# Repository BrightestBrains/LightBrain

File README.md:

# LightBrain

## Overview

The initial motivation was to develop a compact and relatively versatile light control device. Communicating with colleagues interested in electronics, I made a few design decisions so that the functionality would meet a number of requests: wide power supply voltages, protection, buttons, DMX support, shifted ouputs.

* ESP32-WROOM module
* four level shifted outputs
* 6-30V protected power input
* RS485 chip (DMX Support)
* Convinent buttons and user LED
* Very handy WAGO spring terminals

## Usage

Designed mostly for the usage with [WLED firmware](https://github.com/Aircoookie/WLED) by [Aircookie](https://github.com/Aircoookie)

There is no USB=>UART bridge in design. This was done to make the design smaller and cheaper. In the future, a firmware device with pogopin will be made, but most likely there will be a revision of the entire design. WLED has OTA functionality which can be used in case of update the firmware.

The board comes with a few examples that I wrote to test the functionality of the board. I really like [micropython](https://micropython.org/), which works fine on these boards. Very handy for prototyping, the buttons and custom LED makes it interactive. Unfortunately, I never got around to running DMX with python. Then I wrote an example using the SparkFunDMX library, which works like a charm.

## Appearance and Examples

Illustration of working WLED:

https://user-images.githubusercontent.com/8849896/159166993-72adfaef-fdb5-461d-86bc-35848b8165a1.mp4

https://user-images.githubusercontent.com/8849896/159166995-e5065d50-ee23-4bfb-9fdf-d8251501cd79.mp4

https://user-images.githubusercontent.com/8849896/159166997-b3421e14-9344-47e1-aa16-2b2efedc7f29.mp4

Illustration of working DMX:

https://user-images.githubusercontent.com/8849896/159167005-f4b18b29-a19e-47f2-82c6-617aa11a5b83.mp4

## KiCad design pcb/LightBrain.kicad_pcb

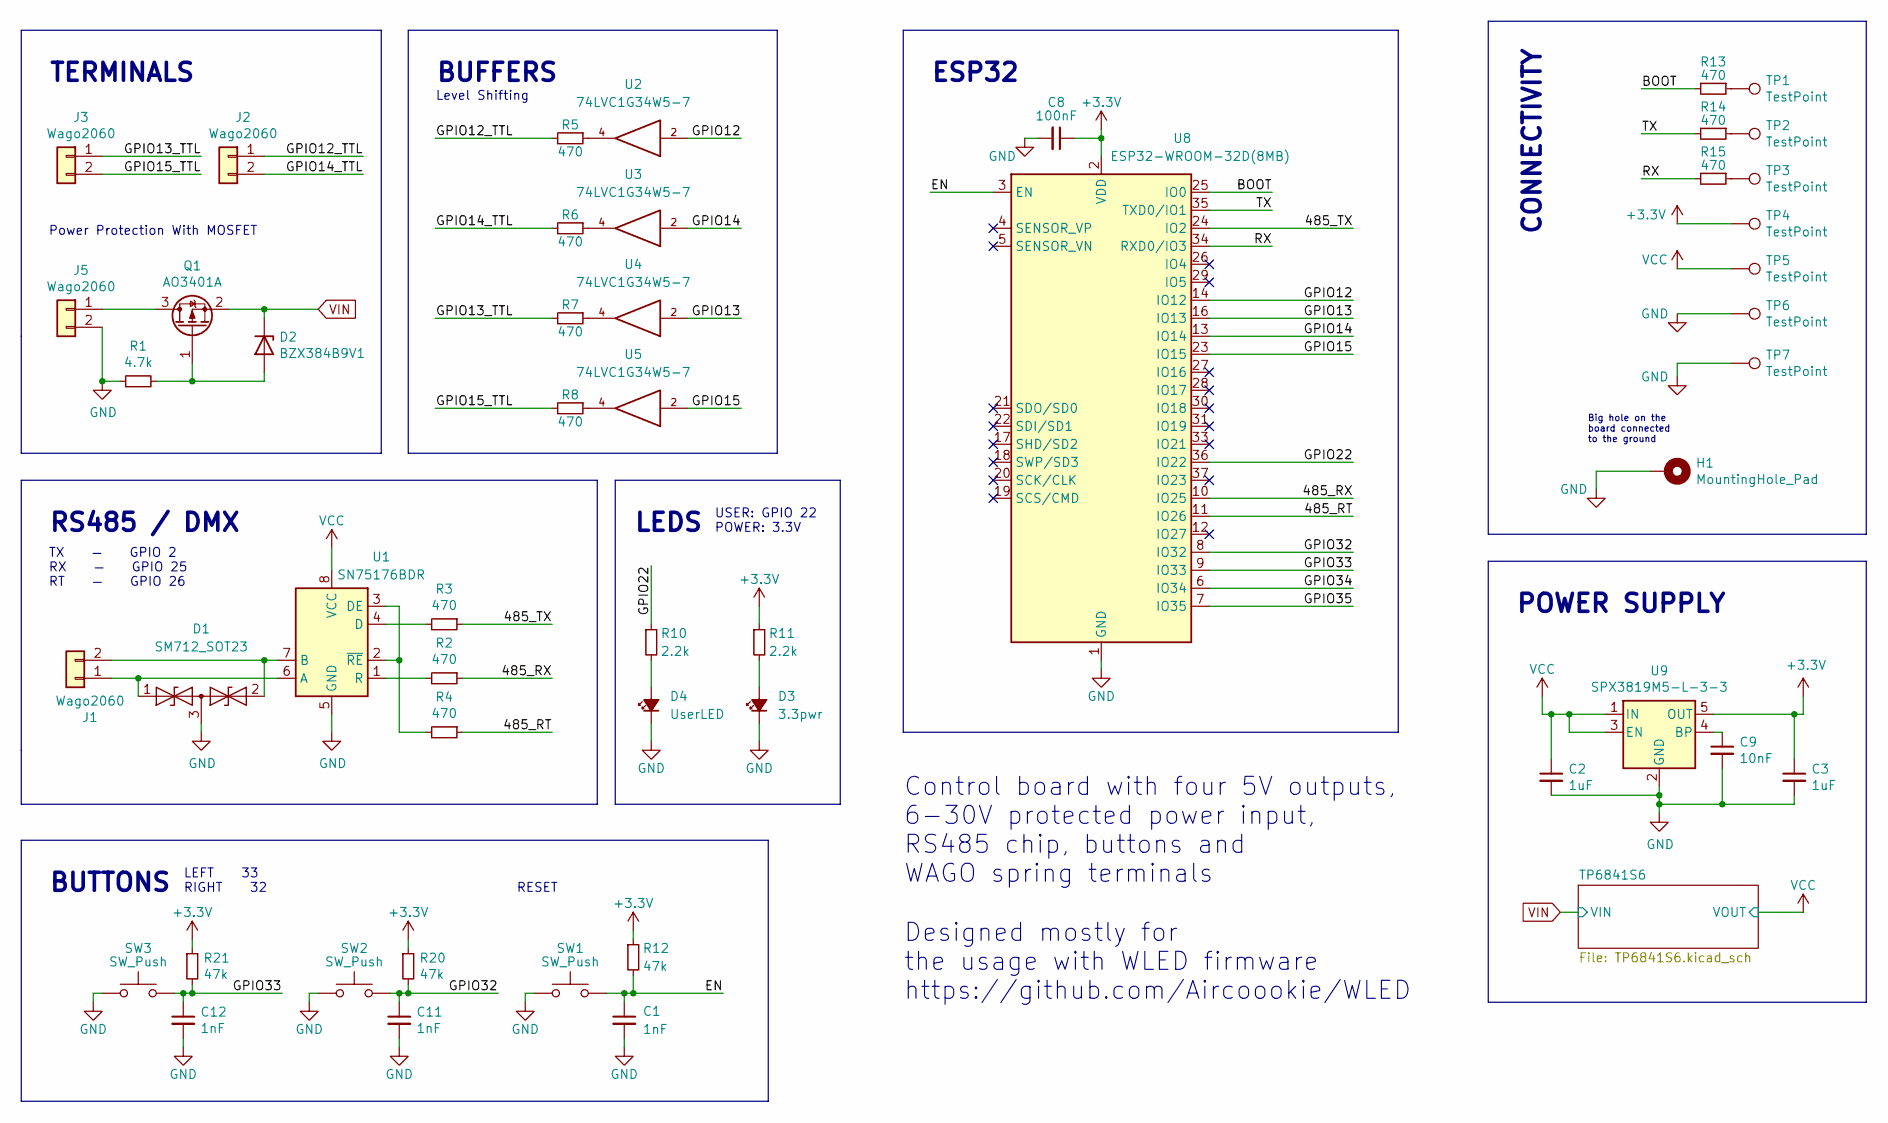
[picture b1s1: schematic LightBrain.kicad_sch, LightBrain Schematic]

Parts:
C1, C11, C12: 1nF; C_0402_1005Metric; JLCPCB Part # C1523
C2, C3: 1uF; C_0402_1005Metric; JLCPCB Part # C52923
C8: 100nF; C_0402_1005Metric; JLCPCB Part # C307331
C9: 10nF; C_0402_1005Metric; JLCPCB Part # C15195
D1: SM712_SOT23; SOT-23; JLCPCB Part # C32677
D2: BZX384B9V1; D_SOD-323; JLCPCB Part # C241956
D3: 3.3pwr; LED_0805_2012Metric; JLCPCB Part # C2296
D4: UserLED; LED_0805_2012Metric; JLCPCB Part # C2296
H1: MountingHole_Pad; MountingHole_2.5mm_Pad
J1, J2, J3, J5: Wago2060; JLCPCB Part # C2765055
Q1: AO3401A; SOT-23; JLCPCB Part # C15127
R1: 4.7k; R_0805_2012Metric; JLCPCB Part # C17673
R2, R3, R4, R5, R6, R7, R8, R13, R14, R15: 470; R_0402_1005Metric; JLCPCB Part # C25117
R10, R11: 2.2k; R_0402_1005Metric; JLCPCB Part # C25879
R12, R20, R21: 47k; R_0402_1005Metric; JLCPCB Part # C25792
SW1, SW2, SW3: SW_Push; SW-SMD-2_2.9x3.9x1.7; JLCPCB Part # C843669
TP1, TP2, TP3, TP4, TP5, TP6, TP7: TestPoint; TestPoint_My
U1: SN75176BDR; SOIC-8_3.9x4.9mm_P1.27mm; JLCPCB Part # C7063
U2, U3, U4, U5: 74LVC1G34W5-7; SOT25; JLCPCB Part # C526347
U8: ESP32-WROOM-32D(8MB); ESP32-WROOM-32; JLCPCB Part # C529577
U9: SPX3819M5-L-3-3; SOT-23-5; JLCPCB Part # C9055

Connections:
+3V3: C3.1, C8.1, R11.1, R12.1, R20.1, R21.1, TP4.1, U8.2 (VDD), U9.5 (OUT)
/485_RT: R4.1, U8.11 (IO26)
/485_RX: R2.1, U8.10 (IO25)
/485_TX: R3.1, U8.24 (IO2)
/BOOT: R13.2, U8.25 (IO0)
/GPIO12: U2.2, U8.14 (IO12)
/GPIO12_TTL: J2.1, R5.2
/GPIO13: U4.2, U8.16 (IO13)
/GPIO13_TTL: J3.1, R7.2
/GPIO14: U3.2, U8.13 (IO14)
/GPIO14_TTL: J2.2, R6.2
/GPIO15: U5.2, U8.23 (IO15)
/GPIO15_TTL: J3.2, R8.2
/GPIO32: C11.1, R20.2, SW2.2, U8.8 (IO32)
/GPIO33: C12.1, R21.2, SW3.2, U8.9 (IO33)
/GPIO34: U8.6 (IO34)
/GPIO35: U8.7 (IO35)
/GPIO36: R10.1, U8.36 (IO22)
/RX: R15.2, U8.34 (RXD0/IO3)
/TX: R14.2, U8.35 (TXD0/IO1)
GND: C1.2, C2.2, C3.2, C8.2, C9.2, C11.2, C12.2, D1.3 (common), D3.1 (K), D4.1 (K), H1.1, J5.2, R1.1, SW1.1, SW2.1, SW3.1, TP6.1, TP7.1, U1.5 (GND), U2.3 (GND), U3.3 (GND), U4.3 (GND), U5.3 (GND), U8.1 (GND), U8.15 (GND), U8.38 (GND), U8.39 (GND), U9.2 (GND); also elsewhere on the board
unnamed: C1.1, R12.2, SW1.2, U8.3 (EN)
unnamed: C9.1, U9.4 (BP)
unnamed: D1.1 (A1), J1.1, U1.6 (A)
unnamed: D1.2 (A2), J1.2, U1.7 (B)
unnamed: D2.2 (A), Q1.1 (G), R1.2
unnamed: D3.2 (A), R11.2
unnamed: D4.2 (A), R10.2
unnamed: J5.1, Q1.3 (D)
unnamed: R2.2, U1.1 (R)
unnamed: R3.2, U1.4 (D)
unnamed: R4.2, U1.2 (~RE), U1.3 (DE)
unnamed: R5.1, U2.4
unnamed: R6.1, U3.4
unnamed: R7.1, U4.4
unnamed: R8.1, U5.4
unnamed: R13.1, TP1.1
unnamed: R14.1, TP2.1
unnamed: R15.1, TP3.1
VCC: C2.1, TP5.1, U1.8 (VCC), U2.5 (VCC), U3.5 (VCC), U4.5 (VCC), U5.5 (VCC), U9.1 (IN), U9.3 (EN); also elsewhere on the board
VIN: D2.1 (K), Q1.2 (S); also elsewhere on the board

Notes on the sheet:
TERMINALS
ESP32
LEDS
Level Shifting
RESET
RS485 / DMX
Designed mostly for the usage with WLED firmware https://github.com/Aircoookie/WLED
BUFFERS
BUTTONS
Control board with four 5V outputs, 6-30V protected power input, RS485 chip, buttons and WAGO spring terminals
Power Protection With MOSFET
USER: GPIO 22 POWER: 3.3V
POWER SUPPLY
TX — GPIO 2 RX — GPIO 25 RT — GPIO 26
LEFT 33 RIGHT 32
Big hole on the board connected to the ground
CONNECTIVITY

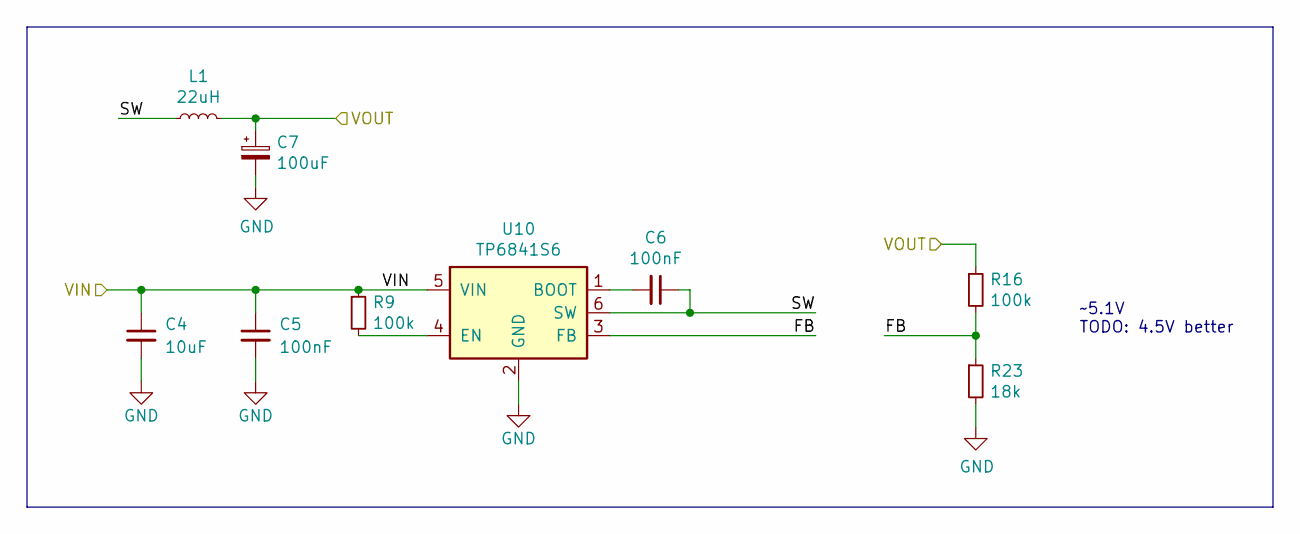
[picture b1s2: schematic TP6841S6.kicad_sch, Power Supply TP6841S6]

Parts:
C4: 10uF; C_0805_2012Metric; JLCPCB Part # C15850
C5: 100nF; C_0805_2012Metric; JLCPCB Part # C28233
C6: 100nF; C_0402_1005Metric; JLCPCB Part # C307331
C7: 100uF; CP_EIA-3528-21_Kemet-B; JLCPCB Part # C115391
L1: 22uH; MWSA0402S; JLCPCB Part # C408340
R9, R16: 100k; R_0402_1005Metric; JLCPCB Part # C25741
R23: 18k; R_0402_1005Metric; JLCPCB Part # C25762
U10: TP6841S6; SOT-23-6; JLCPCB Part # C2844736

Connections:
/TP6841S6/FB: R16.2, R23.1, U10.3 (FB)
/TP6841S6/SW: C6.1, L1.1, U10.6 (SW)
GND: C4.2, C5.2, C7.2, R23.2, U10.2 (GND); also elsewhere on the board
unnamed: C6.2, U10.1 (BOOT)
unnamed: R9.2, U10.4 (EN)
VCC: C7.1, L1.2, R16.1; also elsewhere on the board
VIN: C4.1, C5.1, R9.1, U10.5 (VIN); also elsewhere on the board

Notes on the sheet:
~5.1V TODO: 4.5V better

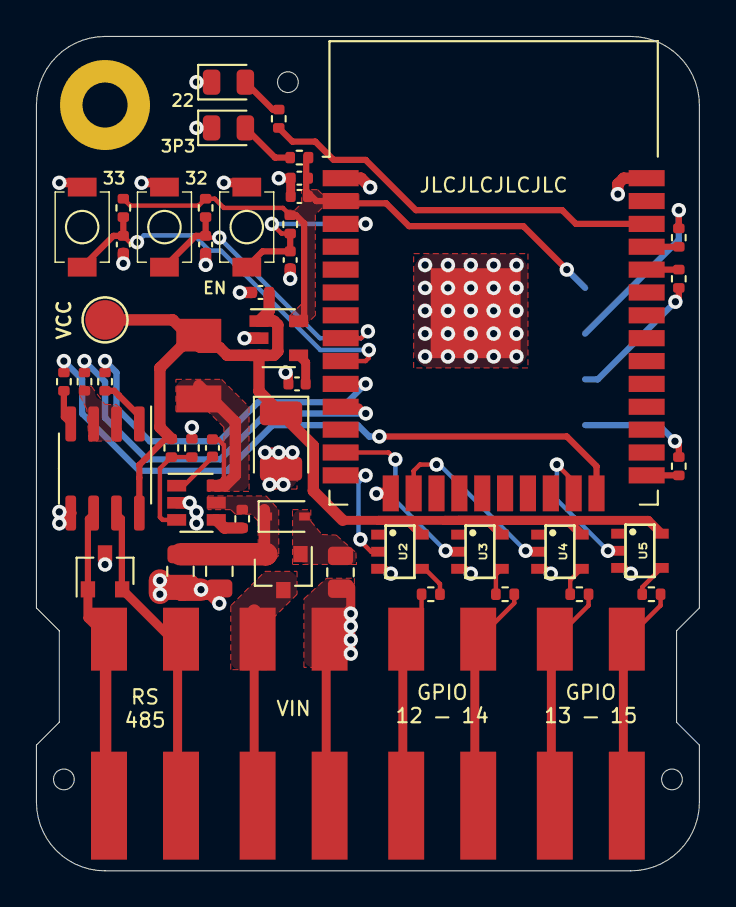
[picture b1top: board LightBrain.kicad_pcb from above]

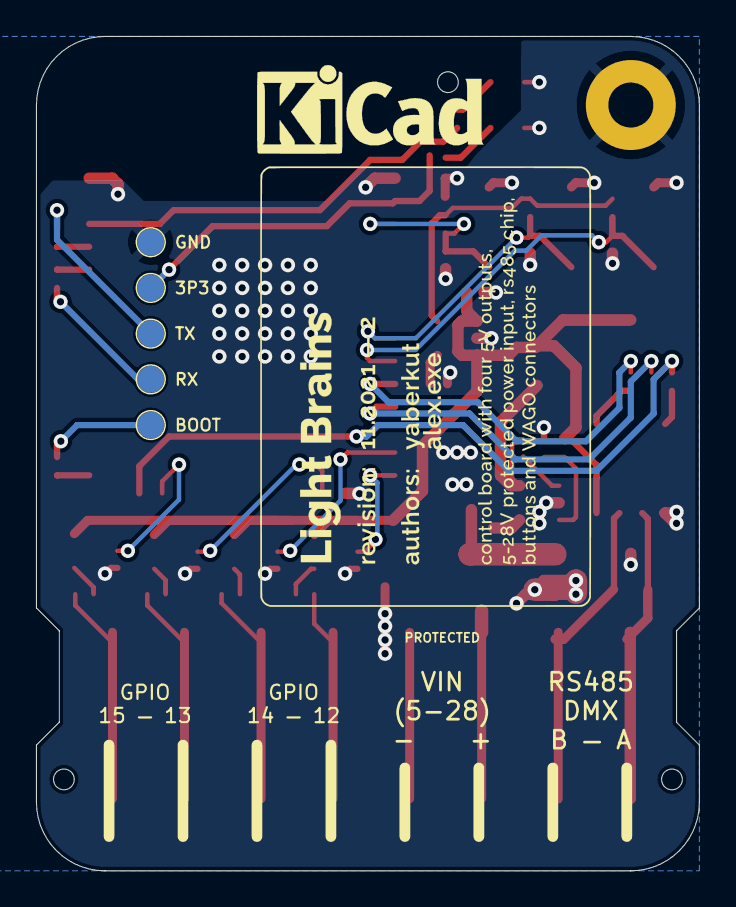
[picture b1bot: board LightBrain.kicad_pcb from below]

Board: 2 copper layers, 36.8 x 46.4 mm, 58 parts (5 on the bottom side), 43 nets.

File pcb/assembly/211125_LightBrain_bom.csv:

Comment,Designator,Footprint,JLCPCB Part #
"1nF Unpolarized capacitor, small symbol","C1,C11,C12",C_0402_1005Metric,C1523
"1uF Unpolarized capacitor, small symbol","C2,C3",C_0402_1005Metric,C52923
"10uF Unpolarized capacitor, small symbol",C4,C_0805_2012Metric,C15850
"100nF Unpolarized capacitor, small symbol",C5,C_0805_2012Metric,C28233
"100nF Unpolarized capacitor, small symbol","C6,C8",C_0402_1005Metric,C307331
"100uF Polarized capacitor, small symbol",C7,CP_EIA-3528-21_Kemet-B,C115391
"10nF Unpolarized capacitor, small symbol",C9,C_0402_1005Metric,C15195
"SM712_SOT23 7V/12V, 600W Asymmetrical TVS Diode Array, SOT-23",D1,SOT-23,C2827658
"BZX384B9V1 300mW Zener Diode, SOD-323",D2,D_SOD-323,C241956
"3.3pwr Light emitting diode, small symbol, filled shape",D3,LED_0805_2012Metric,C2296
"UserLED Light emitting diode, small symbol, filled shape",D4,LED_0805_2012Metric,C2296
"Wago2060 Generic connector, single row, 01x02, script generated (kicad-library-utils/schlib/autogen/connector/)","J1,J2,J3,J5",Wago2060,C2765055
"22uH Inductor, small symbol",L1,MWSA0402S,C408340
"AO3401A -4.0A Id, -30V Vds, P-Channel MOSFET, SOT-23",Q1,SOT-23,C15127
"4.7k Resistor, small symbol",R1,R_0805_2012Metric,C17673
"470 Resistor, small symbol","R2,R3,R4,R5,R6,R7,R8,R13,R14,R15",R_0402_1005Metric,C25117
"100k Resistor, small symbol","R9,R16",R_0402_1005Metric,C25741
"2.2k Resistor, small symbol","R10,R11",R_0402_1005Metric,C25879
"47k Resistor, small symbol","R12,R20,R21",R_0402_1005Metric,C25792
"18k Resistor, small symbol",R23,R_0402_1005Metric,C25762
"SW_Push Push button switch, generic, two pins","SW1,SW2,SW3",SW-SMD-2_2.9x3.9x1.7,C843669
"SN75176BDR Differential RS-422/RS-485 bus transceiver, SOIC-8",U1,SOIC-8_3.9x4.9mm_P1.27mm,C7063
"74LVC1G34W5-7 Single Buffef Gate, Low-Voltage CMOS","U2,U3,U4,U5",SOT25,C526347
"ESP32-WROOM-32D RF Module, ESP32-D0WDQ6 SoC, Wi-Fi 802.11b/g/n, Bluetooth, BLE, 32-bit, 2.7-3.6V, onboard antenna, SMD",U8,ESP32-WROOM-32,C473012
"SPX3819M5-L-3-3 500mA Low drop-out regulator, Fixed Output 3.3V, SOT-23-5",U9,SOT-23-5,C9055
TP6841S6 ,U10,SOT-23-6,C2844736

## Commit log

2022-03-20 Added: Code PCB files Initial structure
2022-03-20 Doc files, slight fixes, initial readme.md content
2022-03-20 changed readme, more photos
2022-03-31 More examples: vvvv, micropython; fix in gerbers; added firmware binary
2022-04-21 add missing footprints pretty
